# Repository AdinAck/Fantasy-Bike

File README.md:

# Fantasy-Bike
 Projects and resources for my electric "fantasy bike".
 
# EVOS
 The "Electric Vehicle Operating System". This is the software responsible for monitoring sensors, controlling components, and displaying the user interface.

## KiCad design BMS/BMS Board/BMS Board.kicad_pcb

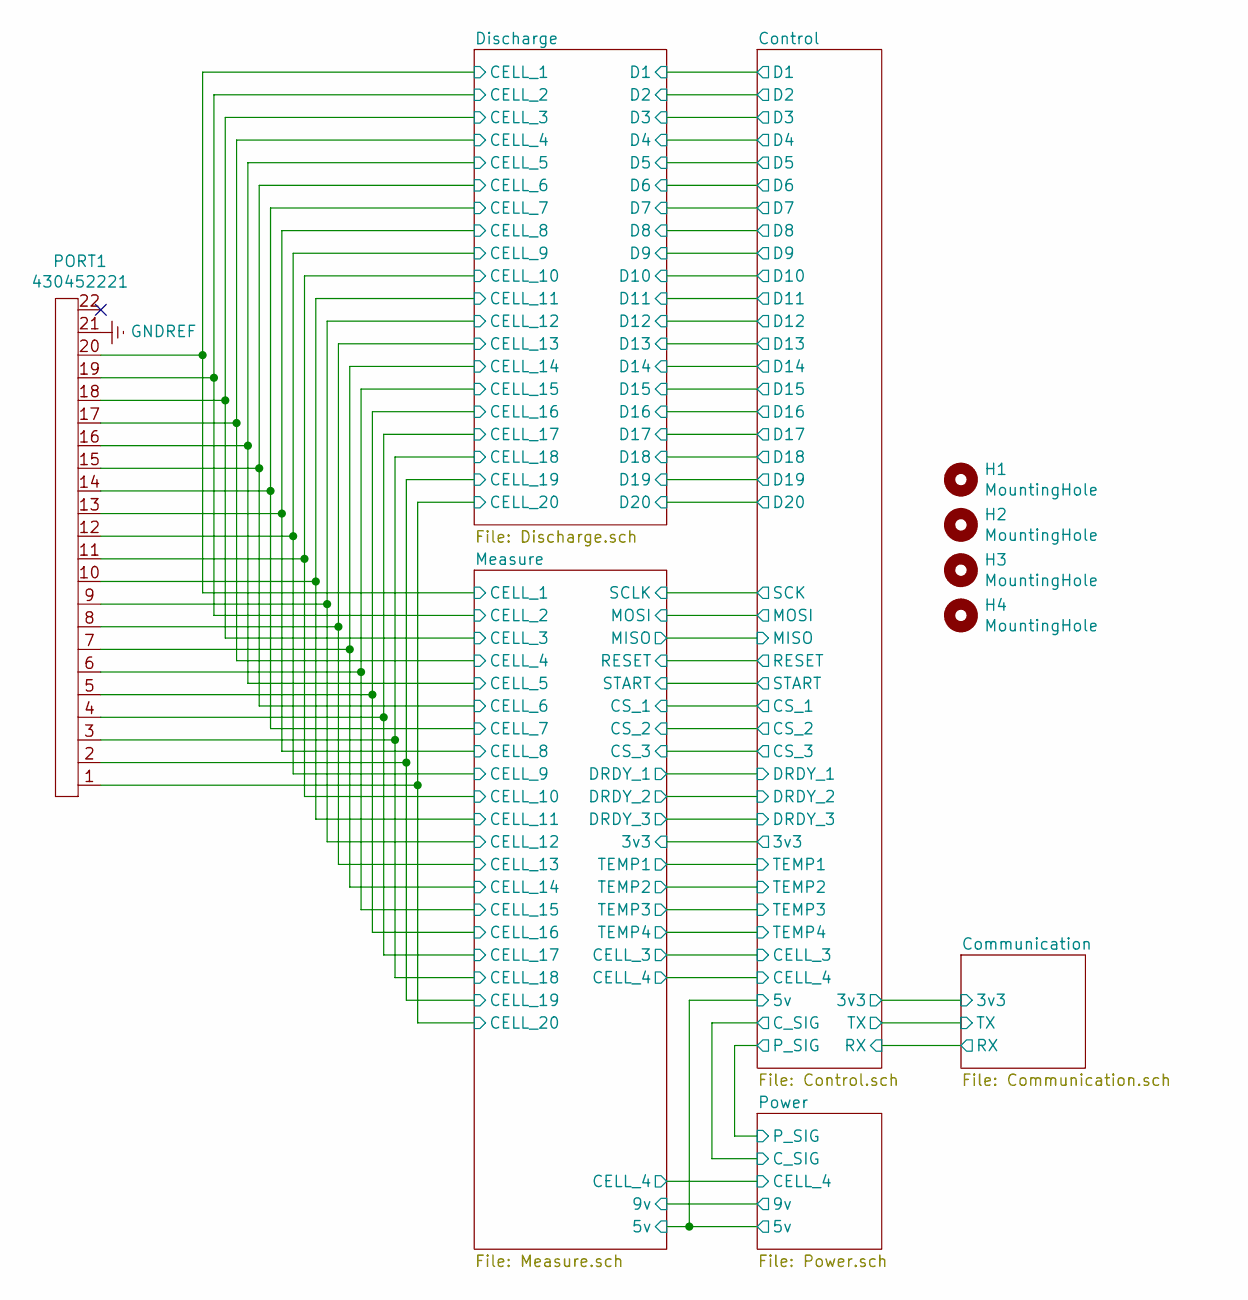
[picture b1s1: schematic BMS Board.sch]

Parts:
H1, H2, H3, H4: MountingHole; MountingHole_4mm_Pad_Better
PORT1: 430452221

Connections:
/Control/CELL_3: PORT1.18; also elsewhere on the board
/Control/CELL_4: PORT1.17; also elsewhere on the board
/Discharge/CELL_1: PORT1.20; also elsewhere on the board
/Discharge/CELL_2: PORT1.19; also elsewhere on the board
/Discharge/CELL_5: PORT1.16; also elsewhere on the board
/Discharge/CELL_6: PORT1.15; also elsewhere on the board
/Discharge/CELL_7: PORT1.14; also elsewhere on the board
/Discharge/CELL_8: PORT1.13; also elsewhere on the board
/Discharge/CELL_9: PORT1.12; also elsewhere on the board
/Discharge/CELL_10: PORT1.11; also elsewhere on the board
/Discharge/CELL_11: PORT1.10; also elsewhere on the board
/Discharge/CELL_12: PORT1.9; also elsewhere on the board
/Discharge/CELL_13: PORT1.8; also elsewhere on the board
/Discharge/CELL_14: PORT1.7; also elsewhere on the board
/Discharge/CELL_15: PORT1.6; also elsewhere on the board
/Discharge/CELL_16: PORT1.5; also elsewhere on the board
/Discharge/CELL_17: PORT1.4; also elsewhere on the board
/Discharge/CELL_18: PORT1.3; also elsewhere on the board
/Discharge/CELL_19: PORT1.2; also elsewhere on the board
/Discharge/CELL_20: PORT1.1; also elsewhere on the board

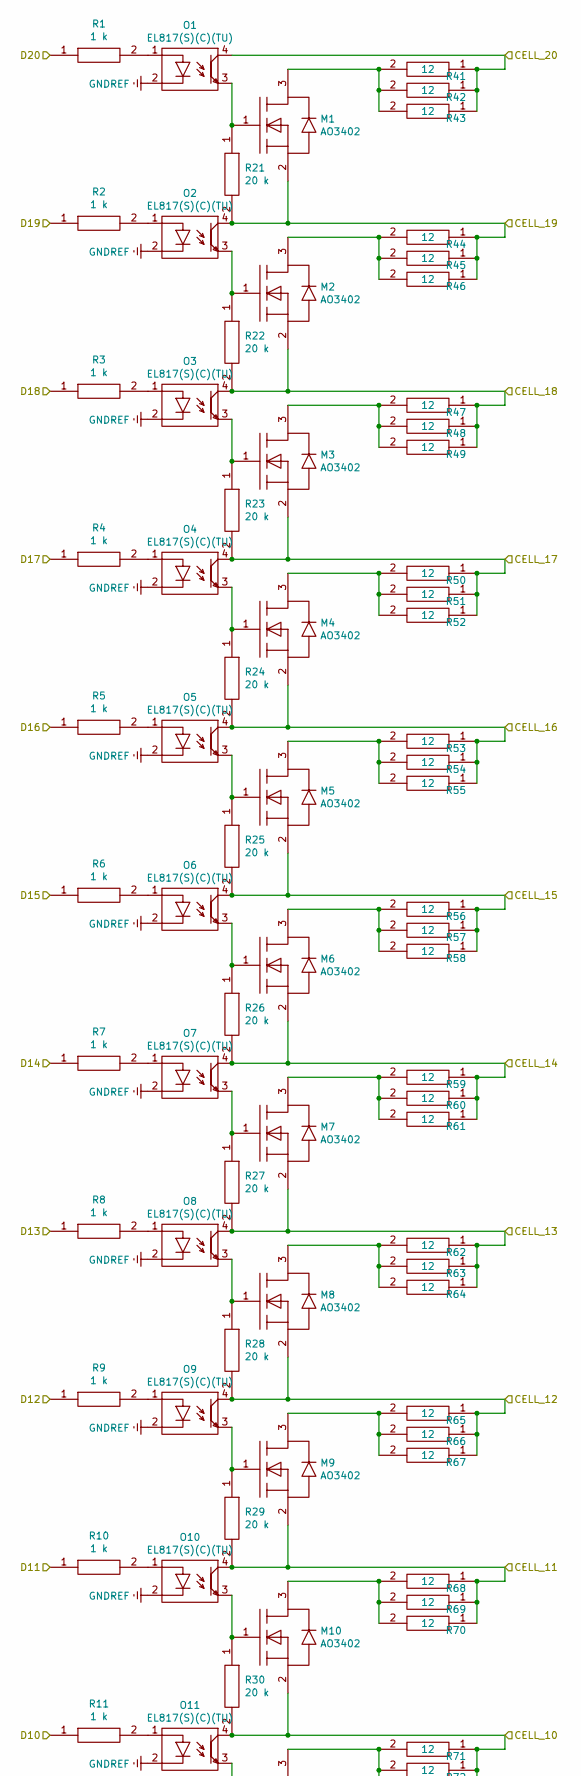
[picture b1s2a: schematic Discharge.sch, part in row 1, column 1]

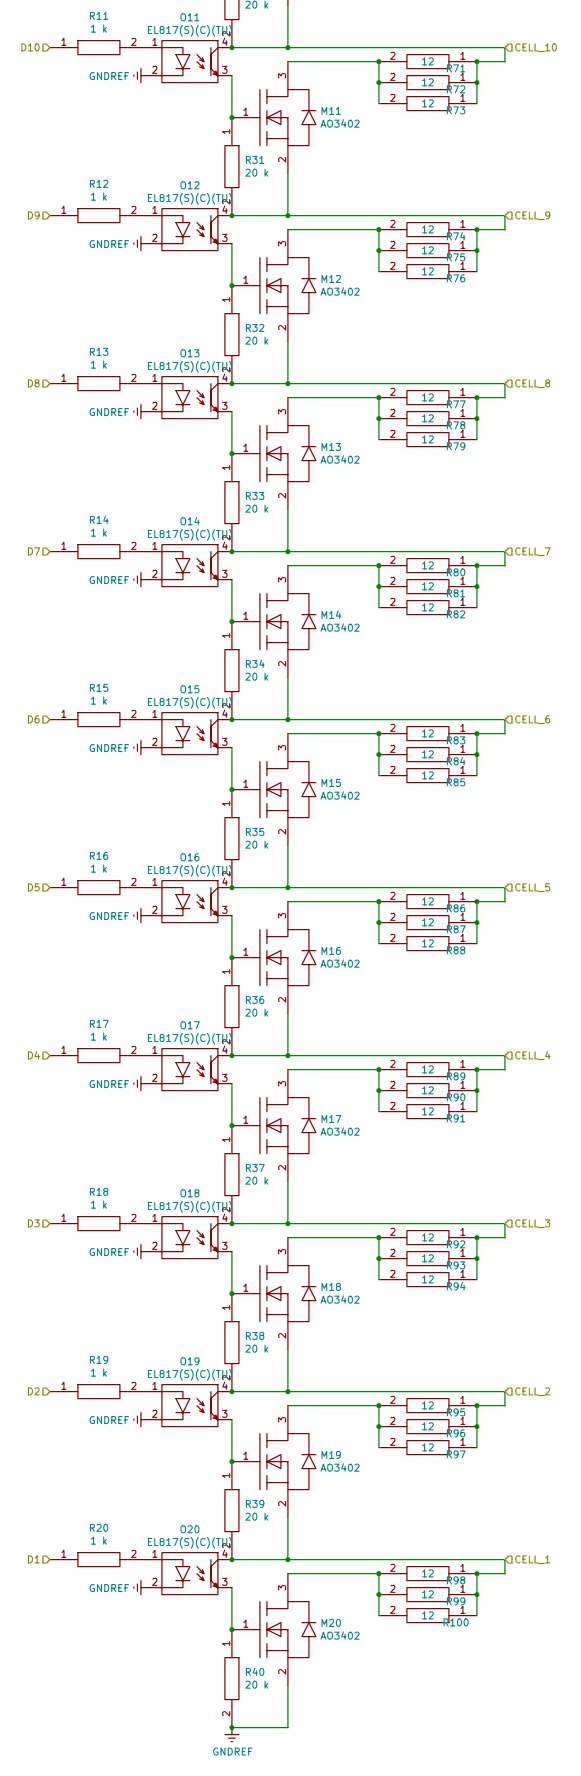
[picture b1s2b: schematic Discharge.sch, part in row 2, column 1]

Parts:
M1, M2, M3, M4, M5, M6, M7, M8, M9, M10, M11, M12, M13, M14, M15, M16, M17, M18, M19, M20: AO3402; SOT-23
O1, O2, O3, O4, O5, O6, O7, O8, O9, O10, O11, O12, O13, O14, O15, O16, O17, O18, O19, O20: EL817(S)(C)(TU); SOP-4_Optocoupler
R1, R2, R3, R4, R5, R6, R7, R8, R9, R10, R11, R12, R13, R14, R15, R16, R17, R18, R19, R20: ERJ-6ENF1001V; RESC2012X70N; Mouser Part Number 667-ERJ-6ENF1001V
R21, R22, R23, R24, R25, R26, R27, R28, R29, R30, R31, R32, R33, R34, R35, R36, R37, R38, R39, R40: ERJ-S06F2002V; RESC2012X70N; Mouser Part Number 667-ERJ-S06F2002V
R41, R42, R43, R44, R45, R46, R47, R48, R49, R50, R51, R52, R53, R54, R55, R56, R57, R58, R59, R60, R61, R62, R63, R64, R65, R66, R67, R68, R69, R70, R71, R72, R73, R74, R75, R76, R77, R78, R79, R80, R81, R82, R83, R84, R85, R86, R87, R88, R89, R90, R91, R92, R93, R94, R95, R96, R97, R98, R99, R100: CRGP2512F12R; RESC6432X65N; Mouser Part Number 279-CRGP2512F12R

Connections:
/Control/CELL_3: M17.2 (S), O18.4 (Collector), R37.2, R92.1, R93.1, R94.1; also elsewhere on the board
/Control/CELL_4: M16.2 (S), O17.4 (Collector), R36.2, R89.1, R90.1, R91.1; also elsewhere on the board
/Control/D1: R20.1; also elsewhere on the board
/Control/D2: R19.1; also elsewhere on the board
/Control/D3: R18.1; also elsewhere on the board
/Control/D4: R17.1; also elsewhere on the board
/Control/D5: R16.1; also elsewhere on the board
/Control/D6: R15.1; also elsewhere on the board
/Control/D7: R14.1; also elsewhere on the board
/Control/D8: R13.1; also elsewhere on the board
/Control/D9: R12.1; also elsewhere on the board
/Control/D10: R11.1; also elsewhere on the board
/Control/D11: R10.1; also elsewhere on the board
/Control/D12: R9.1; also elsewhere on the board
/Control/D13: R8.1; also elsewhere on the board
/Control/D14: R7.1; also elsewhere on the board
/Control/D15: R6.1; also elsewhere on the board
/Control/D16: R5.1; also elsewhere on the board
/Control/D17: R4.1; also elsewhere on the board
/Control/D18: R3.1; also elsewhere on the board
/Control/D19: R2.1; also elsewhere on the board
/Control/D20: R1.1; also elsewhere on the board
/Discharge/CELL_1: M19.2 (S), O20.4 (Collector), R39.2, R98.1, R99.1, R100.1; also elsewhere on the board
/Discharge/CELL_2: M18.2 (S), O19.4 (Collector), R38.2, R95.1, R96.1, R97.1; also elsewhere on the board
/Discharge/CELL_5: M15.2 (S), O16.4 (Collector), R35.2, R86.1, R87.1, R88.1; also elsewhere on the board
/Discharge/CELL_6: M14.2 (S), O15.4 (Collector), R34.2, R83.1, R84.1, R85.1; also elsewhere on the board
/Discharge/CELL_7: M13.2 (S), O14.4 (Collector), R33.2, R80.1, R81.1, R82.1; also elsewhere on the board
/Discharge/CELL_8: M12.2 (S), O13.4 (Collector), R32.2, R77.1, R78.1, R79.1; also elsewhere on the board
/Discharge/CELL_9: M11.2 (S), O12.4 (Collector), R31.2, R74.1, R75.1, R76.1; also elsewhere on the board
/Discharge/CELL_10: M10.2 (S), O11.4 (Collector), R30.2, R71.1, R72.1, R73.1; also elsewhere on the board
/Discharge/CELL_11: M9.2 (S), O10.4 (Collector), R29.2, R68.1, R69.1, R70.1; also elsewhere on the board
/Discharge/CELL_12: M8.2 (S), O9.4 (Collector), R28.2, R65.1, R66.1, R67.1; also elsewhere on the board
/Discharge/CELL_13: M7.2 (S), O8.4 (Collector), R27.2, R62.1, R63.1, R64.1; also elsewhere on the board
/Discharge/CELL_14: M6.2 (S), O7.4 (Collector), R26.2, R59.1, R60.1, R61.1; also elsewhere on the board
/Discharge/CELL_15: M5.2 (S), O6.4 (Collector), R25.2, R56.1, R57.1, R58.1; also elsewhere on the board
/Discharge/CELL_16: M4.2 (S), O5.4 (Collector), R24.2, R53.1, R54.1, R55.1; also elsewhere on the board
/Discharge/CELL_17: M3.2 (S), O4.4 (Collector), R23.2, R50.1, R51.1, R52.1; also elsewhere on the board
/Discharge/CELL_18: M2.2 (S), O3.4 (Collector), R22.2, R47.1, R48.1, R49.1; also elsewhere on the board
/Discharge/CELL_19: M1.2 (S), O2.4 (Collector), R21.2, R44.1, R45.1, R46.1; also elsewhere on the board
/Discharge/CELL_20: O1.4 (Collector), R41.1, R42.1, R43.1; also elsewhere on the board
unnamed: M1.1 (G), O1.3 (Emitter), R21.1
unnamed: M1.3 (D), R41.2, R42.2, R43.2
unnamed: M2.1 (G), O2.3 (Emitter), R22.1
unnamed: M2.3 (D), R44.2, R45.2, R46.2
unnamed: M3.1 (G), O3.3 (Emitter), R23.1
unnamed: M3.3 (D), R47.2, R48.2, R49.2
unnamed: M4.1 (G), O4.3 (Emitter), R24.1
unnamed: M4.3 (D), R50.2, R51.2, R52.2
unnamed: M5.1 (G), O5.3 (Emitter), R25.1
unnamed: M5.3 (D), R53.2, R54.2, R55.2
unnamed: M6.1 (G), O6.3 (Emitter), R26.1
unnamed: M6.3 (D), R56.2, R57.2, R58.2
unnamed: M7.1 (G), O7.3 (Emitter), R27.1
unnamed: M7.3 (D), R59.2, R60.2, R61.2
unnamed: M8.1 (G), O8.3 (Emitter), R28.1
unnamed: M8.3 (D), R62.2, R63.2, R64.2
unnamed: M9.1 (G), O9.3 (Emitter), R29.1
unnamed: M9.3 (D), R65.2, R66.2, R67.2
unnamed: M10.1 (G), O10.3 (Emitter), R30.1
unnamed: M10.3 (D), R68.2, R69.2, R70.2
unnamed: M11.1 (G), O11.3 (Emitter), R31.1
unnamed: M11.3 (D), R71.2, R72.2, R73.2
unnamed: M12.1 (G), O12.3 (Emitter), R32.1
unnamed: M12.3 (D), R74.2, R75.2, R76.2
unnamed: M13.1 (G), O13.3 (Emitter), R33.1
unnamed: M13.3 (D), R77.2, R78.2, R79.2
unnamed: M14.1 (G), O14.3 (Emitter), R34.1
unnamed: M14.3 (D), R80.2, R81.2, R82.2
unnamed: M15.1 (G), O15.3 (Emitter), R35.1
unnamed: M15.3 (D), R83.2, R84.2, R85.2
unnamed: M16.1 (G), O16.3 (Emitter), R36.1
unnamed: M16.3 (D), R86.2, R87.2, R88.2
unnamed: M17.1 (G), O17.3 (Emitter), R37.1
unnamed: M17.3 (D), R89.2, R90.2, R91.2
unnamed: M18.1 (G), O18.3 (Emitter), R38.1
unnamed: M18.3 (D), R92.2, R93.2, R94.2
unnamed: M19.1 (G), O19.3 (Emitter), R39.1
unnamed: M19.3 (D), R95.2, R96.2, R97.2
unnamed: M20.1 (G), O20.3 (Emitter), R40.1
unnamed: M20.3 (D), R98.2, R99.2, R100.2
unnamed: O1.1 (Anode), R1.2
unnamed: O2.1 (Anode), R2.2
unnamed: O3.1 (Anode), R3.2
unnamed: O4.1 (Anode), R4.2
unnamed: O5.1 (Anode), R5.2
unnamed: O6.1 (Anode), R6.2
unnamed: O7.1 (Anode), R7.2
unnamed: O8.1 (Anode), R8.2
unnamed: O9.1 (Anode), R9.2
unnamed: O10.1 (Anode), R10.2
unnamed: O11.1 (Anode), R11.2
unnamed: O12.1 (Anode), R12.2
unnamed: O13.1 (Anode), R13.2
unnamed: O14.1 (Anode), R14.2
unnamed: O15.1 (Anode), R15.2
unnamed: O16.1 (Anode), R16.2
unnamed: O17.1 (Anode), R17.2
unnamed: O18.1 (Anode), R18.2
unnamed: O19.1 (Anode), R19.2
unnamed: O20.1 (Anode), R20.2

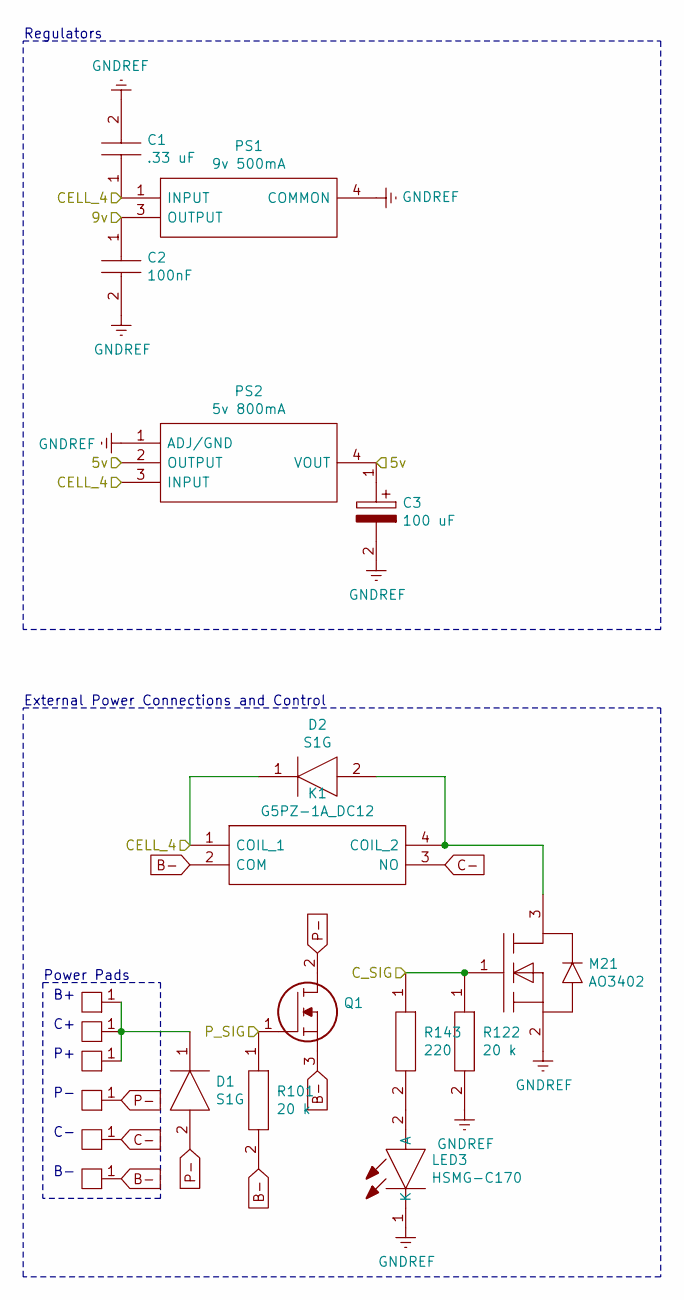
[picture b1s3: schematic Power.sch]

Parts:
C1: 08053C334KAT2A; CAPC2012X140N; Mouser Part Number 581-08053C334KAT2A
C2: 0805ZC104MAT2A; CAPC2012X94N; Mouser Part Number 581-0805ZC104MAT2A
C3: TPSC107K010R0150; CAPPM6032X280N; Mouser Part Number 581-TPSC107K010R0150
D1, D2: S1G; DIOM5227X250N; Mouser Part Number 512-S1G
K1: G5PZ-1A_DC12; G5PZ1ADC12; Mouser Part Number 653-G5PZ-1ADC12
LED3: HSMG-C170; LEDC2012X80N; Mouser Part Number 630-HSMG-C170
M21: AO3402; SOT-23
P1, P2, P3, P4, P5, P6: Power_Pad
PS1: UA78M09CKVURG3; Voltage, Current 9v 500mA; Mouser Part Number 595-UA78M09CKVURG3
PS2: LM1117MPX-5.0_NOPB; SOT230P700X180-4N; Voltage, Current 5v 800mA; Mouser Part Number 926-LM1117MPX5.0NOPB
Q1: STD12N60DM2AG; STD13N60DM2; Mouser Part Number 511-STD12N60DM2AG
R101, R122: ERJ-S06F2002V; RESC2012X70N; Mouser Part Number 667-ERJ-S06F2002V
R143: ERJ-P06F2200V; RESC2012X70N; Mouser Part Number 667-ERJ-P06F2200V

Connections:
9v: C2.1, PS1.3 (OUTPUT); also elsewhere on the board
/Control/5v: C3.1, PS2.2 (OUTPUT), PS2.4 (VOUT); also elsewhere on the board
/Control/CELL_4: C1.1, D2.1, K1.1 (COIL_1), PS1.1 (INPUT), PS2.3 (INPUT); also elsewhere on the board
/Control/C_SIG: M21.1 (G), R122.1, R143.1; also elsewhere on the board
/Control/P_SIG: Q1.1, R101.1; also elsewhere on the board
B-: K1.2 (COM), P6.1, Q1.3, R101.2
C-: K1.3 (NO), P5.1
unnamed: D1.1, P1.1, P2.1, P3.1
unnamed: D2.2, K1.4 (COIL_2), M21.3 (D)
unnamed: LED3.2 (A), R143.2
P-: D1.2, P4.1, Q1.2

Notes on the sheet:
Power Pads
External Power Connections and Control
Regulators

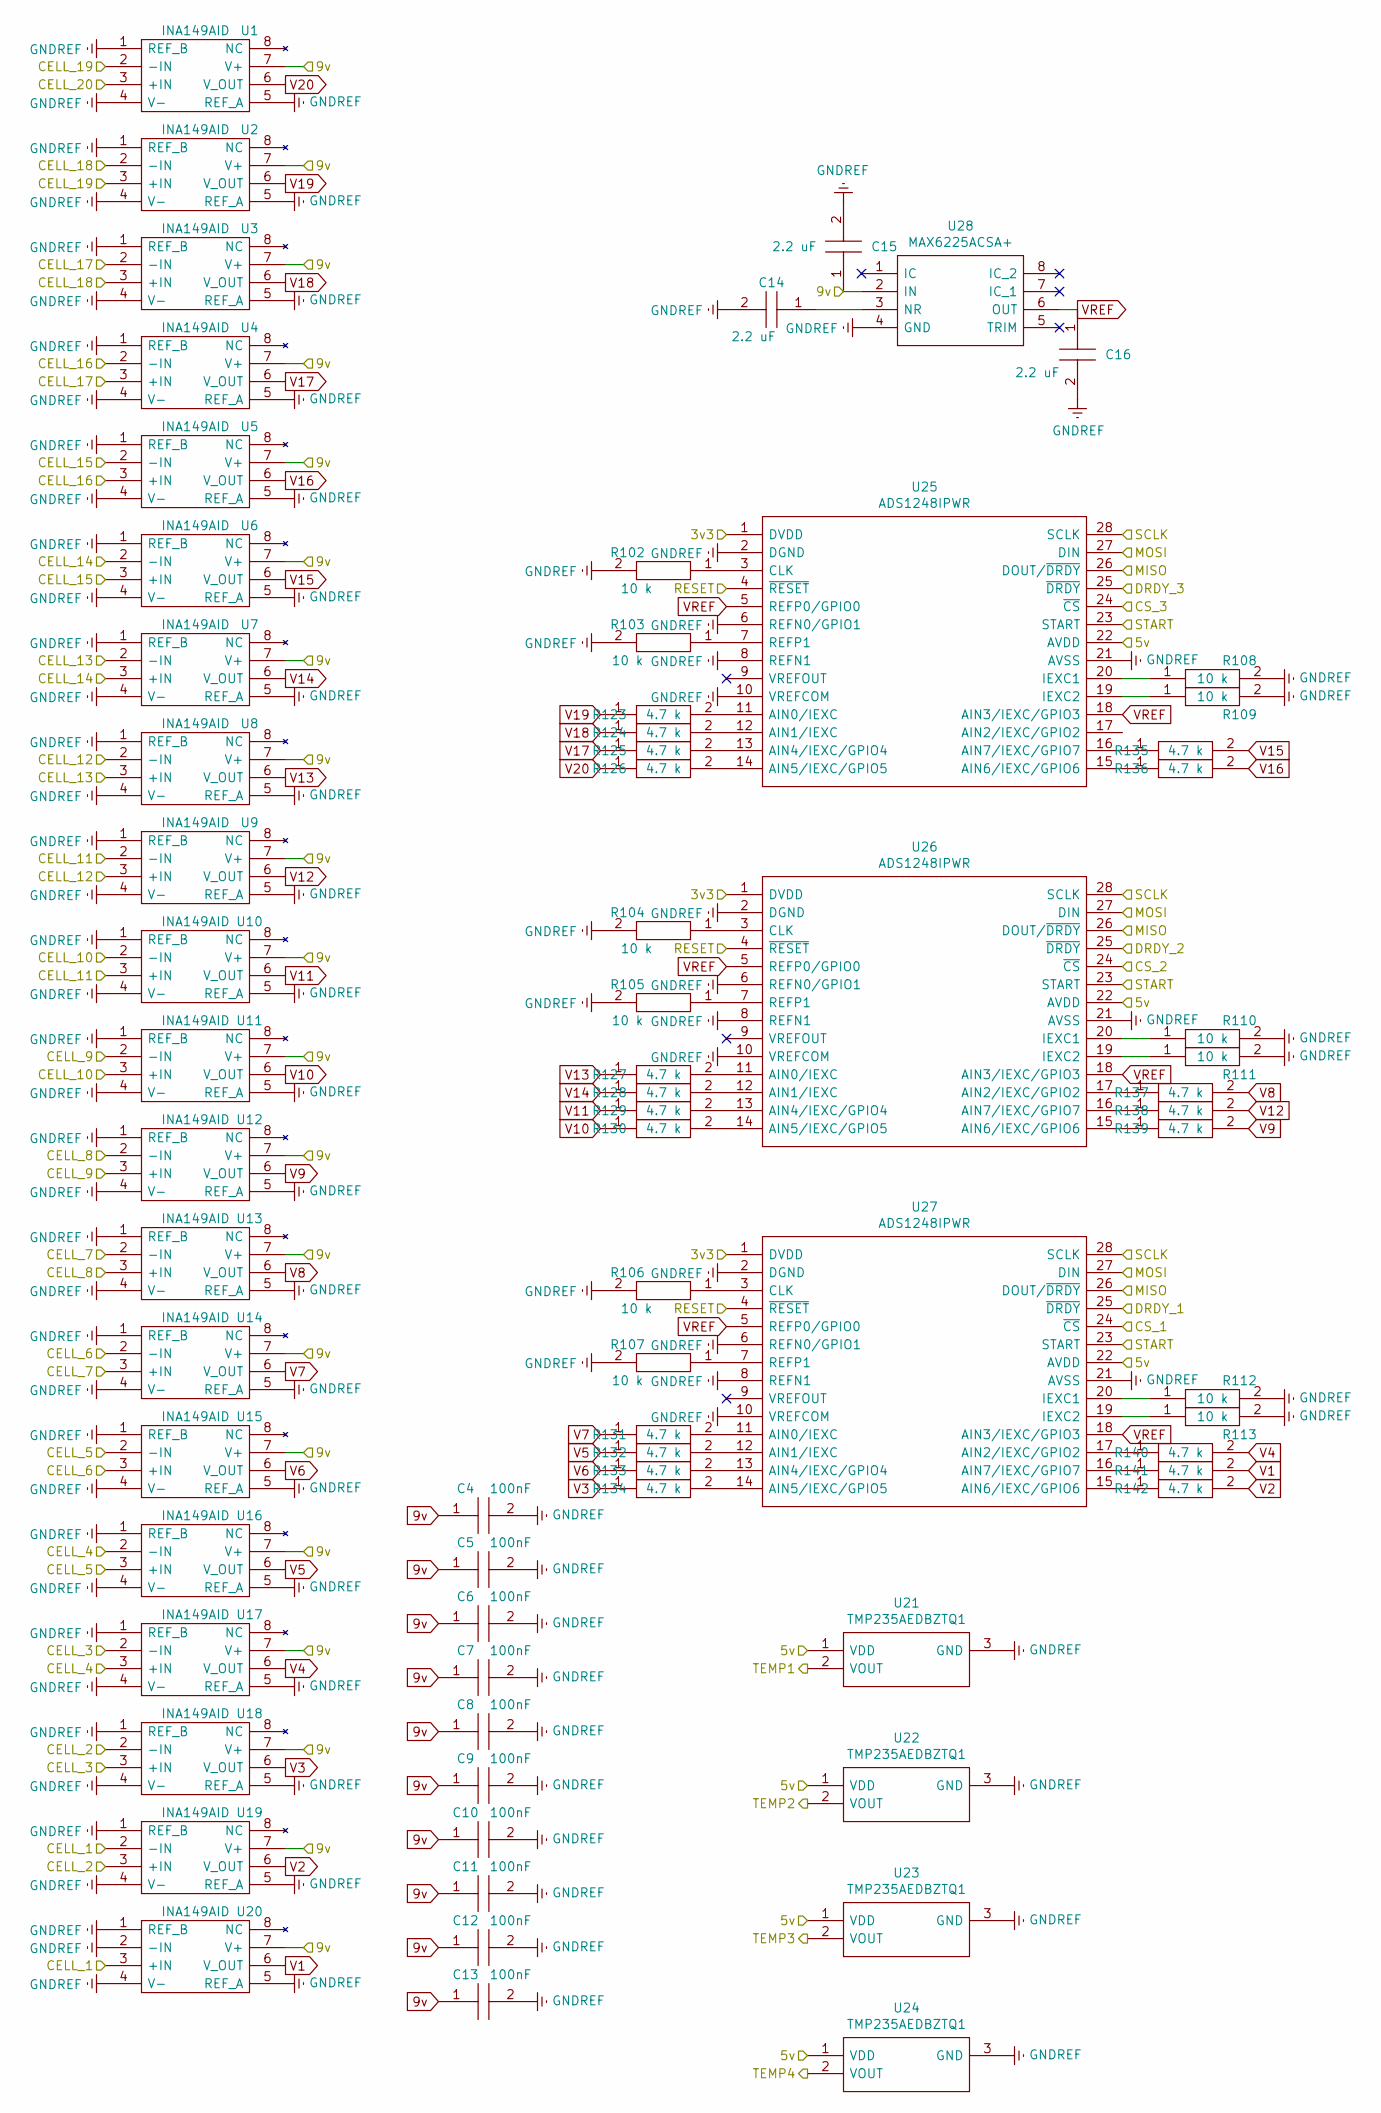
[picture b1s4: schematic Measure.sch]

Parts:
C4, C5, C6, C7, C8, C9, C10, C11, C12, C13: 0805ZC104MAT2A; CAPC2012X94N; Mouser Part Number 581-0805ZC104MAT2A
C14, C15, C16: 08053C225K4T2A; CAPC2012X94N; Manufacturer_Part_Number 08053C225K4T2A
R102, R103, R104, R105, R106, R107, R108, R109, R110, R111, R112, R113: ERJ-UP6J103v; RESC2012X70N; Mouser Part Number 667-ERJ-UP6J103V
R123, R124, R125, R126, R127, R128, R129, R130, R131, R132, R133, R134, R135, R136, R137, R138, R139, R140, R141, R142: ERJ-S06J472V; RESC2012X70N; Mouser Part Number 667-ERJ-S06J472V
U1, U2, U3, U4, U5, U6, U7, U8, U9, U10, U11, U12, U13, U14, U15, U16, U17, U18, U19, U20: INA149AID; SOIC127P600X175-8N; Mouser Part Number 595-INA149AID
U21, U22, U23, U24: TMP235AEDBZTQ1; SOT95P237X112-3N; Mouser Part Number 595-TMP235AEDBZTQ1
U25, U26, U27: ADS1248IPWR; SOP65P640X120-28N; Mouser Part Number 595-ADS1248IPWR
U28: MAX6225ACSA+; SOIC127P600X175-8N; Mouser Part Number 700-MAX6225ACSA

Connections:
9v: C4.1, C5.1, C6.1, C7.1, C8.1, C9.1, C10.1, C11.1, C12.1, C13.1, C15.1, U1.7 (V+), U2.7 (V+), U3.7 (V+), U4.7 (V+), U5.7 (V+), U6.7 (V+), U7.7 (V+), U8.7 (V+), U9.7 (V+), U10.7 (V+), U11.7 (V+), U12.7 (V+), U13.7 (V+), U14.7 (V+), U15.7 (V+), U16.7 (V+), U17.7 (V+), U18.7 (V+), U19.7 (V+), U20.7 (V+), U28.2 (IN); also elsewhere on the board
/Control/5v: U21.1 (VDD), U22.1 (VDD), U23.1 (VDD), U24.1 (VDD), U25.22 (AVDD), U26.22 (AVDD), U27.22 (AVDD); also elsewhere on the board
/Control/CELL_3: U17.2 (-IN), U18.3 (+IN); also elsewhere on the board
/Control/CELL_4: U16.2 (-IN), U17.3 (+IN); also elsewhere on the board
/Control/CS_1: U27.24 (~CS); also elsewhere on the board
/Control/CS_2: U26.24 (~CS); also elsewhere on the board
/Control/CS_3: U25.24 (~CS); also elsewhere on the board
/Control/DRDY_1: U27.25 (~DRDY); also elsewhere on the board
/Control/DRDY_2: U26.25 (~DRDY); also elsewhere on the board
/Control/DRDY_3: U25.25 (~DRDY); also elsewhere on the board
/Control/MISO: U25.26 (DOUT/~DRDY), U26.26 (DOUT/~DRDY), U27.26 (DOUT/~DRDY); also elsewhere on the board
/Control/MOSI: U25.27 (DIN), U26.27 (DIN), U27.27 (DIN); also elsewhere on the board
/Control/RESET: U25.4 (~RESET), U26.4 (~RESET), U27.4 (~RESET); also elsewhere on the board
/Control/SCK: U25.28 (SCLK), U26.28 (SCLK), U27.28 (SCLK); also elsewhere on the board
/Control/START: U25.23 (START), U26.23 (START), U27.23 (START); also elsewhere on the board
/Control/TEMP1: U21.2 (VOUT); also elsewhere on the board
/Control/TEMP2: U22.2 (VOUT); also elsewhere on the board
/Control/TEMP3: U23.2 (VOUT); also elsewhere on the board
/Control/TEMP4: U24.2 (VOUT); also elsewhere on the board
/Discharge/CELL_1: U19.2 (-IN), U20.3 (+IN); also elsewhere on the board
/Discharge/CELL_2: U18.2 (-IN), U19.3 (+IN); also elsewhere on the board
/Discharge/CELL_5: U15.2 (-IN), U16.3 (+IN); also elsewhere on the board
/Discharge/CELL_6: U14.2 (-IN), U15.3 (+IN); also elsewhere on the board
/Discharge/CELL_7: U13.2 (-IN), U14.3 (+IN); also elsewhere on the board
/Discharge/CELL_8: U12.2 (-IN), U13.3 (+IN); also elsewhere on the board
/Discharge/CELL_9: U11.2 (-IN), U12.3 (+IN); also elsewhere on the board
/Discharge/CELL_10: U10.2 (-IN), U11.3 (+IN); also elsewhere on the board
/Discharge/CELL_11: U9.2 (-IN), U10.3 (+IN); also elsewhere on the board
/Discharge/CELL_12: U8.2 (-IN), U9.3 (+IN); also elsewhere on the board
/Discharge/CELL_13: U7.2 (-IN), U8.3 (+IN); also elsewhere on the board
/Discharge/CELL_14: U6.2 (-IN), U7.3 (+IN); also elsewhere on the board
/Discharge/CELL_15: U5.2 (-IN), U6.3 (+IN); also elsewhere on the board
/Discharge/CELL_16: U4.2 (-IN), U5.3 (+IN); also elsewhere on the board
/Discharge/CELL_17: U3.2 (-IN), U4.3 (+IN); also elsewhere on the board
/Discharge/CELL_18: U2.2 (-IN), U3.3 (+IN); also elsewhere on the board
/Discharge/CELL_19: U1.2 (-IN), U2.3 (+IN); also elsewhere on the board
/Discharge/CELL_20: U1.3 (+IN); also elsewhere on the board
unnamed: C14.1, U28.3 (NR)
unnamed: R102.1, U25.3 (CLK)
unnamed: R103.1, U25.7 (REFP1)
unnamed: R104.1, U26.3 (CLK)
unnamed: R105.1, U26.7 (REFP1)
unnamed: R106.1, U27.3 (CLK)
unnamed: R107.1, U27.7 (REFP1)
unnamed: R108.1, U25.20 (IEXC1)
unnamed: R109.1, U25.19 (IEXC2)
unnamed: R110.1, U26.20 (IEXC1)
unnamed: R111.1, U26.19 (IEXC2)
unnamed: R112.1, U27.20 (IEXC1)
unnamed: R113.1, U27.19 (IEXC2)
unnamed: R123.2, U25.11 (AIN0/IEXC)
unnamed: R124.2, U25.12 (AIN1/IEXC)
unnamed: R125.2, U25.13 (AIN4/IEXC/GPIO4)
unnamed: R126.2, U25.14 (AIN5/IEXC/GPIO5)
unnamed: R127.2, U26.11 (AIN0/IEXC)
unnamed: R128.2, U26.12 (AIN1/IEXC)
unnamed: R129.2, U26.13 (AIN4/IEXC/GPIO4)
unnamed: R130.2, U26.14 (AIN5/IEXC/GPIO5)
unnamed: R131.2, U27.11 (AIN0/IEXC)
unnamed: R132.2, U27.12 (AIN1/IEXC)
unnamed: R133.2, U27.13 (AIN4/IEXC/GPIO4)
unnamed: R134.2, U27.14 (AIN5/IEXC/GPIO5)
unnamed: R135.1, U25.16 (AIN7/IEXC/GPIO7)
unnamed: R136.1, U25.15 (AIN6/IEXC/GPIO6)
unnamed: R137.1, U26.17 (AIN2/IEXC/GPIO2)
unnamed: R138.1, U26.16 (AIN7/IEXC/GPIO7)
unnamed: R139.1, U26.15 (AIN6/IEXC/GPIO6)
unnamed: R140.1, U27.17 (AIN2/IEXC/GPIO2)
unnamed: R141.1, U27.16 (AIN7/IEXC/GPIO7)
unnamed: R142.1, U27.15 (AIN6/IEXC/GPIO6)
V1: R141.2, U20.6 (V_OUT)
V2: R142.2, U19.6 (V_OUT)
V3: R134.1, U18.6 (V_OUT)
V4: R140.2, U17.6 (V_OUT)
V5: R132.1, U16.6 (V_OUT)
V6: R133.1, U15.6 (V_OUT)
V7: R131.1, U14.6 (V_OUT)
V8: R137.2, U13.6 (V_OUT)
V9: R139.2, U12.6 (V_OUT)
V10: R130.1, U11.6 (V_OUT)
V11: R129.1, U10.6 (V_OUT)
V12: R138.2, U9.6 (V_OUT)
V13: R127.1, U8.6 (V_OUT)
V14: R128.1, U7.6 (V_OUT)
V15: R135.2, U6.6 (V_OUT)
V16: R136.2, U5.6 (V_OUT)
V17: R125.1, U4.6 (V_OUT)
V18: R124.1, U3.6 (V_OUT)
V19: R123.1, U2.6 (V_OUT)
V20: R126.1, U1.6 (V_OUT)
VREF: C16.1, U25.5 (REFP0/GPIO0), U25.18 (AIN3/IEXC/GPIO3), U26.5 (REFP0/GPIO0), U26.18 (AIN3/IEXC/GPIO3), U27.5 (REFP0/GPIO0), U27.18 (AIN3/IEXC/GPIO3), U28.6 (OUT)

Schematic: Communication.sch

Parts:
C17: 0805ZC104MAT2A; CAPC2012X94N; Mouser Part Number 581-0805ZC104MAT2A
J1: 10129379-904002BLF; HDRRA4W67P0X254_1X4_1016X254X241P; Mouser Part Number 649-1012937990402BLF
LED1, LED2: HSML-C170-T0000; LEDC2012X90N; Mouser Part Number 630-HSML-C170-T0000
R114, R115: ERJ-6ENF5600V; RESC2012X70N; Mouser Part Number 667-ERJ-6ENF5600V
R116, R117: ERJ-P06F2200V; RESC2012X70N; Mouser Part Number 667-ERJ-P06F2200V

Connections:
/Communication/TX: R114.1, R116.2; also elsewhere on the board
unnamed 68: C17.1, J1.1; also elsewhere on the board
unnamed 69: C17.2, J1.4, LED2.1; also elsewhere on the board
unnamed 72: R114.2; also elsewhere on the board
unnamed 74: J1.2; also elsewhere on the board
unnamed 75: R115.1; also elsewhere on the board
unnamed: J1.3, R115.2, R117.2
unnamed: LED1.2, R116.1
unnamed: LED2.2, R117.1

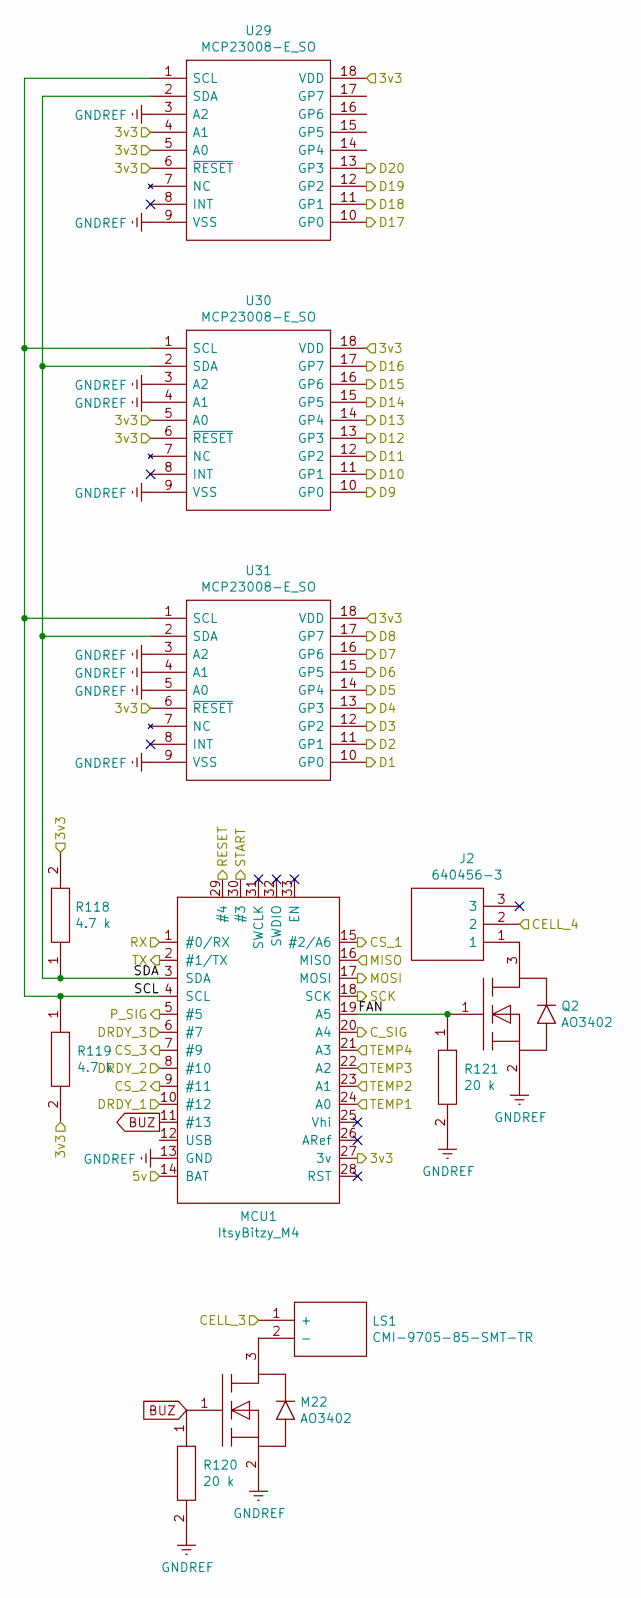
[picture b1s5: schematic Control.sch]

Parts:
J2: 640456-3; HDRV3W107P0X254_1X3_762X572X1080P; Mouser Part Number 571-6404563
LS1: CMI-9705-85-SMT-TR; CMI970585SMTTR; Mouser Part Number 490-CMI-9705-85SMTTR
M22: AO3402; SOT-23
MCU1: ItsyBitzy_M4; Adafruit_ItsyBitsy_M4
Q2: AO3402; SOT-23
R118, R119: ERJ-S06J472V; RESC2012X70N; Mouser Part Number 667-ERJ-S06J472V
R120, R121: ERJ-S06F2002V; RESC2012X70N; Mouser Part Number 667-ERJ-S06F2002V
U29, U30, U31: MCP23008-E_SO; SOIC127P1030X265-18N; Mouser Part Number 579-MCP23008-E/SO

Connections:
/Communication/RX: MCU1.1 (#0/RX); also elsewhere on the board
/Communication/TX: MCU1.2 (#1/TX); also elsewhere on the board
/Control/5v: MCU1.14 (BAT); also elsewhere on the board
/Control/CELL_3: LS1.1 (+); also elsewhere on the board
/Control/CELL_4: J2.2; also elsewhere on the board
/Control/CS_1: MCU1.15 (#2/A6); also elsewhere on the board
/Control/CS_2: MCU1.9 (#11); also elsewhere on the board
/Control/CS_3: MCU1.7 (#9); also elsewhere on the board
/Control/C_SIG: MCU1.20 (A4); also elsewhere on the board
/Control/D1: U31.10 (GP0); also elsewhere on the board
/Control/D2: U31.11 (GP1); also elsewhere on the board
/Control/D3: U31.12 (GP2); also elsewhere on the board
/Control/D4: U31.13 (GP3); also elsewhere on the board
/Control/D5: U31.14 (GP4); also elsewhere on the board
/Control/D6: U31.15 (GP5); also elsewhere on the board
/Control/D7: U31.16 (GP6); also elsewhere on the board
/Control/D8: U31.17 (GP7); also elsewhere on the board
/Control/D9: U30.10 (GP0); also elsewhere on the board
/Control/D10: U30.11 (GP1); also elsewhere on the board
/Control/D11: U30.12 (GP2); also elsewhere on the board
/Control/D12: U30.13 (GP3); also elsewhere on the board
/Control/D13: U30.14 (GP4); also elsewhere on the board
/Control/D14: U30.15 (GP5); also elsewhere on the board
/Control/D15: U30.16 (GP6); also elsewhere on the board
/Control/D16: U30.17 (GP7); also elsewhere on the board
/Control/D17: U29.10 (GP0); also elsewhere on the board
/Control/D18: U29.11 (GP1); also elsewhere on the board
/Control/D19: U29.12 (GP2); also elsewhere on the board
/Control/D20: U29.13 (GP3); also elsewhere on the board
/Control/DRDY_1: MCU1.10 (#12); also elsewhere on the board
/Control/DRDY_2: MCU1.8 (#10); also elsewhere on the board
/Control/DRDY_3: MCU1.6 (#7); also elsewhere on the board
/Control/FAN: MCU1.19 (A5), Q2.1 (G), R121.1
/Control/MISO: MCU1.16 (MISO); also elsewhere on the board
/Control/MOSI: MCU1.17 (MOSI); also elsewhere on the board
/Control/P_SIG: MCU1.5 (#5); also elsewhere on the board
/Control/RESET: MCU1.29 (#4); also elsewhere on the board
/Control/SCK: MCU1.18 (SCK); also elsewhere on the board
/Control/SCL: MCU1.4 (SCL), R119.1, U29.1 (SCL), U30.1 (SCL), U31.1 (SCL)
/Control/SDA: MCU1.3 (SDA), R118.1, U29.2 (SDA), U30.2 (SDA), U31.2 (SDA)
/Control/START: MCU1.30 (#3); also elsewhere on the board
/Control/TEMP1: MCU1.24 (A0); also elsewhere on the board
/Control/TEMP2: MCU1.23 (A1); also elsewhere on the board
/Control/TEMP3: MCU1.22 (A2); also elsewhere on the board
/Control/TEMP4: MCU1.21 (A3); also elsewhere on the board
BUZ: M22.1 (G), MCU1.11 (#13), R120.1
unnamed: J2.1, Q2.3 (D)
unnamed: LS1.2 (-), M22.3 (D)

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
